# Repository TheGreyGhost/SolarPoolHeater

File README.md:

# SolarPoolHeater
Arduino controller for solar pool heating

An arduino project used to control a solar heating system for a swimming pool.

Uses DS18B20 one-wire temperature sensors, an ethernet shield based on WizNet W5100 (including SD card), and 
  a D51307 real time clock module

Three github projects are used for these:
• SolarPoolHeater (Arduino) - contains code and circuit diagrams for the Arduino which controls the heating components.
• AutomationWebServerCode (Raspberry Pi) - contains the python code used to retrieve data from the Arduino and store it in the database on the RPi
• SwimmingPoolWebServer (Raspberry Pi) - contains the web server code (php) used to display the monitoring data stored in the database

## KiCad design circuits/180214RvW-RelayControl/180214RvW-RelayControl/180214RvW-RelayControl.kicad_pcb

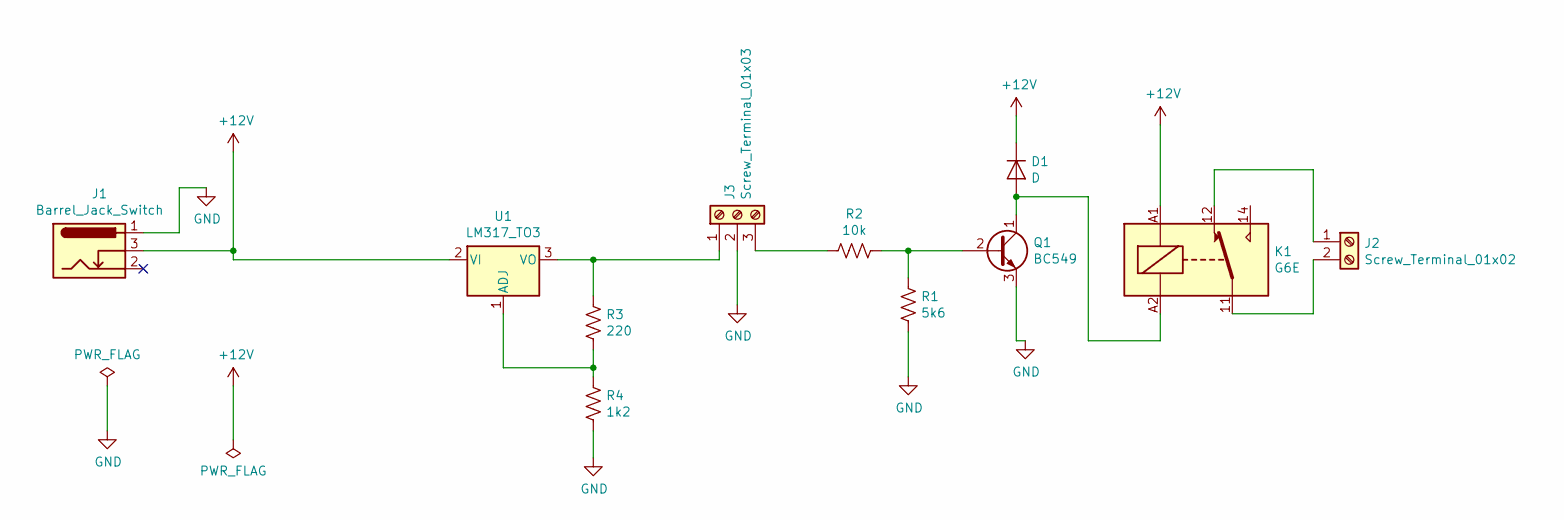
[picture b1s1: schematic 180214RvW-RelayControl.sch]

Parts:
D1: D; D_DO-34_SOD68_P7.62mm_Horizontal
J1: Barrel_Jack_Switch; BarrelJack_Horizontal
J2: Screw_Terminal_01x02; TerminalBlock_Altech_AK300-2_P5.00mm
J3: Screw_Terminal_01x03; TerminalBlock_Altech_AK300-3_P5.00mm
K1: G6E; Relay_SPDT_Finder_40.41
Q1: BC549; TO-92_Inline
R1: 5k6; R_Axial_DIN0411_L9.9mm_D3.6mm_P20.32mm_Horizontal
R2: 10k; R_Axial_DIN0411_L9.9mm_D3.6mm_P20.32mm_Horizontal
R3: 220; R_Axial_DIN0411_L9.9mm_D3.6mm_P20.32mm_Horizontal
R4: 1k2; R_Axial_DIN0411_L9.9mm_D3.6mm_P20.32mm_Horizontal
U1: LM317_TO3; TO-220-3_Horizontal_TabDown

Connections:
+12V: D1.1 (K), J1.3, K1.A1, U1.2 (VI)
GND: J1.1, J3.2, Q1.3 (E), R1.2, R4.2
unnamed: D1.2 (A), K1.A2, Q1.1 (C)
unnamed: J2.1, K1.12
unnamed: J2.2, K1.11
unnamed: J3.1, R3.1, U1.3 (VO)
unnamed: J3.3, R2.1
unnamed: Q1.2 (B), R1.1, R2.2
unnamed: R3.2, R4.1, U1.1 (ADJ)

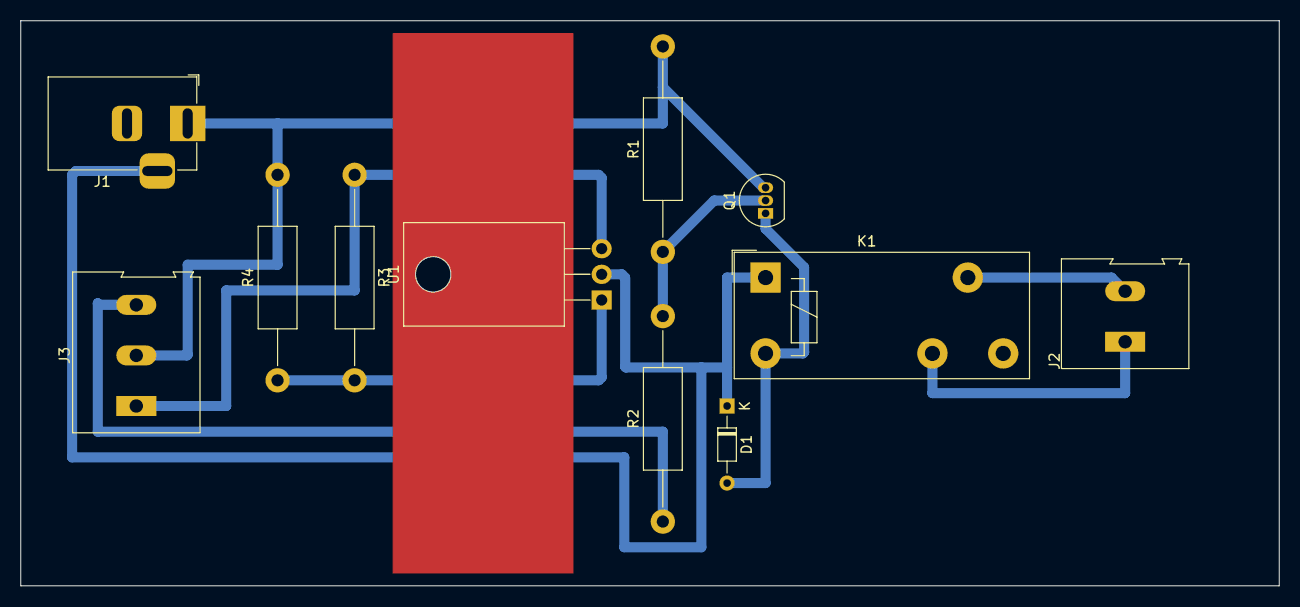
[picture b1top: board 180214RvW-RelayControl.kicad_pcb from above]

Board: 2 copper layers, 124.5 x 55.9 mm, 11 parts (0 on the bottom side), 9 nets.

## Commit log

2018-01-11 :space_invader: Added .gitattributes & .gitignore files
2018-01-11 InitialSetup
    Initial setup and testing of temperature sensors
2018-01-11 Adding error codes
2018-01-12 ongoing
2018-01-13 Compiles. About to add SD support.
    Sketch uses 8780 bytes (27%) of program storage space. Maximum is 32256
    bytes.
    Global variables use 919 bytes (44%) of dynamic memory, leaving 1129
    bytes for local variables. Maximum is 2048 bytes.
2018-01-15 logging
    Basic logging of temperature probes in place
2018-01-17 tweaks
2018-01-17 Splitting into separate files
2018-01-28 Compiles. Ready for debugging.
2018-02-11 Adding 6 sensors. Crashes.
2018-02-11 bugfix
2018-02-11 Make status LED ISR faster
2018-02-13 minor tweak to temp debugging
2018-02-13 status summary now working
2018-02-13 refactoring complete. Need to test datalog.
2018-02-24 circuits and test results
2018-02-24 RealTimeClock implemented
2018-02-27 Implementing solar sensor and pump controls
2018-03-04 LatestForTesting
    Implements basic pump control but isn't currently working
2018-03-04 Basic pump control in place
2018-03-06 more logic on pump control
2018-03-14 Settings and simulations being added
2018-03-15 Ready to debug settings and simulations
2018-03-22 Debugged Settings
2018-03-25 More debugging. Add surge tank level switch
2018-03-26 debugging
2018-03-27 Testing done
2018-03-27 Version 1.0 tested
    HX temp probes, ambient temp probe, solar intensity, surge tank level,
    pump control algorithm.
2018-03-27 test file saved
2018-04-01 BugFixes
2018-04-02 Surge Tank Level Sensor troubleshooting
2018-04-06 minor tweaks to logging
2018-04-14 more data
2018-05-13 Level Sensor replaced and is working
2018-10-18 VariousData
2018-10-22 Testing remote uploads
2018-10-22 Data and Version update
2018-10-24 Adding ethernet test code
2018-10-24 AddingLibraries
2018-10-24 Shuffling Libraries
2018-10-24 Fixing global constant mismatch problem
    DallasTemperature
2018-10-24 fix inconsistent library define problem
2018-10-25 Adding Ethernet
2018-10-27 Bugfix of startup temp probe value
2018-10-27 minor tweak
2018-10-27 Ready for Ethernet test
2018-10-28 Adding Ethernet as parallel to Serial
2018-11-01 ethernet testing info
2018-11-01 Setting up ethernet terminal
2018-11-05 latest log data
2018-11-05 Adding Ethernet terminal. Test harness.
2018-11-05 Fix command
2018-11-05 ethernet terminal
2018-11-07 debug
2018-11-07 terminal over ethernet
2018-11-07 datafilerename
2018-11-07 Fix terminal echo
2018-11-11 More ethernet comms
2018-11-13 Include data update
2018-11-13 Adding Datastream
2018-11-14 working on datastream
2018-11-15 datastream ready for test
2018-11-15 updated log data
2018-11-15 debugging datastream
2018-11-21 more datastream commands
2018-11-22 Datastream ready for testing
2018-12-02 speed testing
2018-12-03 debuggin
2018-12-06 Version 1.12.2
    Version 1.12.2, stripped out debug code sprinkled throughout
2018-12-06 Put some strings into FLASH
2018-12-06 more logged data
2018-12-23 Add free RAM check to print debug info
2019-01-20 Added pump reset.
2019-01-26 more bugfix
2019-01-26 bugagain
2019-01-26 Bug fixed ethernet command
2019-02-07 Add record-last-valid-temperature
2019-02-07 not sure what this is
2019-02-08 adding time zones
2019-02-09 adding timezones and time synch
2019-02-10 Still working on time zones
2019-02-12 timezones and clock resynch
2019-02-13 minor tweaks
2019-02-13 working on time resynch
2019-02-14 timezone ready for testing
2019-02-14 tweak
2019-02-16 time bug fixing
2019-02-19 working again
2019-02-19 getting ready for synch
2019-02-24 test resynch
2019-02-24 moresycnh
2019-02-24 synch working
2019-03-01 test code for resynch
2019-03-01 bugfix resynch and remove debugs
2019-03-12 update while in Zagreb
2019-03-14 readyfordatastream
2019-03-14 local
2019-04-24 Change datastream to include request ID
2019-04-28 debugtrace
2019-04-28 remove debug
2019-10-26 Info about comms protocol
2021-11-08 Adding other boards
2021-11-09 Update some docs
2021-11-09 Overtemp Cutout done
2021-11-10 updating pump relay control board
2021-11-14 Relay Control board complete
2021-11-16 Updating explanation
2022-04-18 Add setup info
